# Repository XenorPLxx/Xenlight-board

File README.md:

# Xenlight-board
In action: https://www.youtube.com/watch?v=SORMGCwLncw

Windows app: https://github.com/XenorPLxx/Xenlight

Atmega16 code: https://github.com/XenorPLxx/Xenlight-driver

EAGLE Schematics: https://github.com/XenorPLxx/Xenlight-board

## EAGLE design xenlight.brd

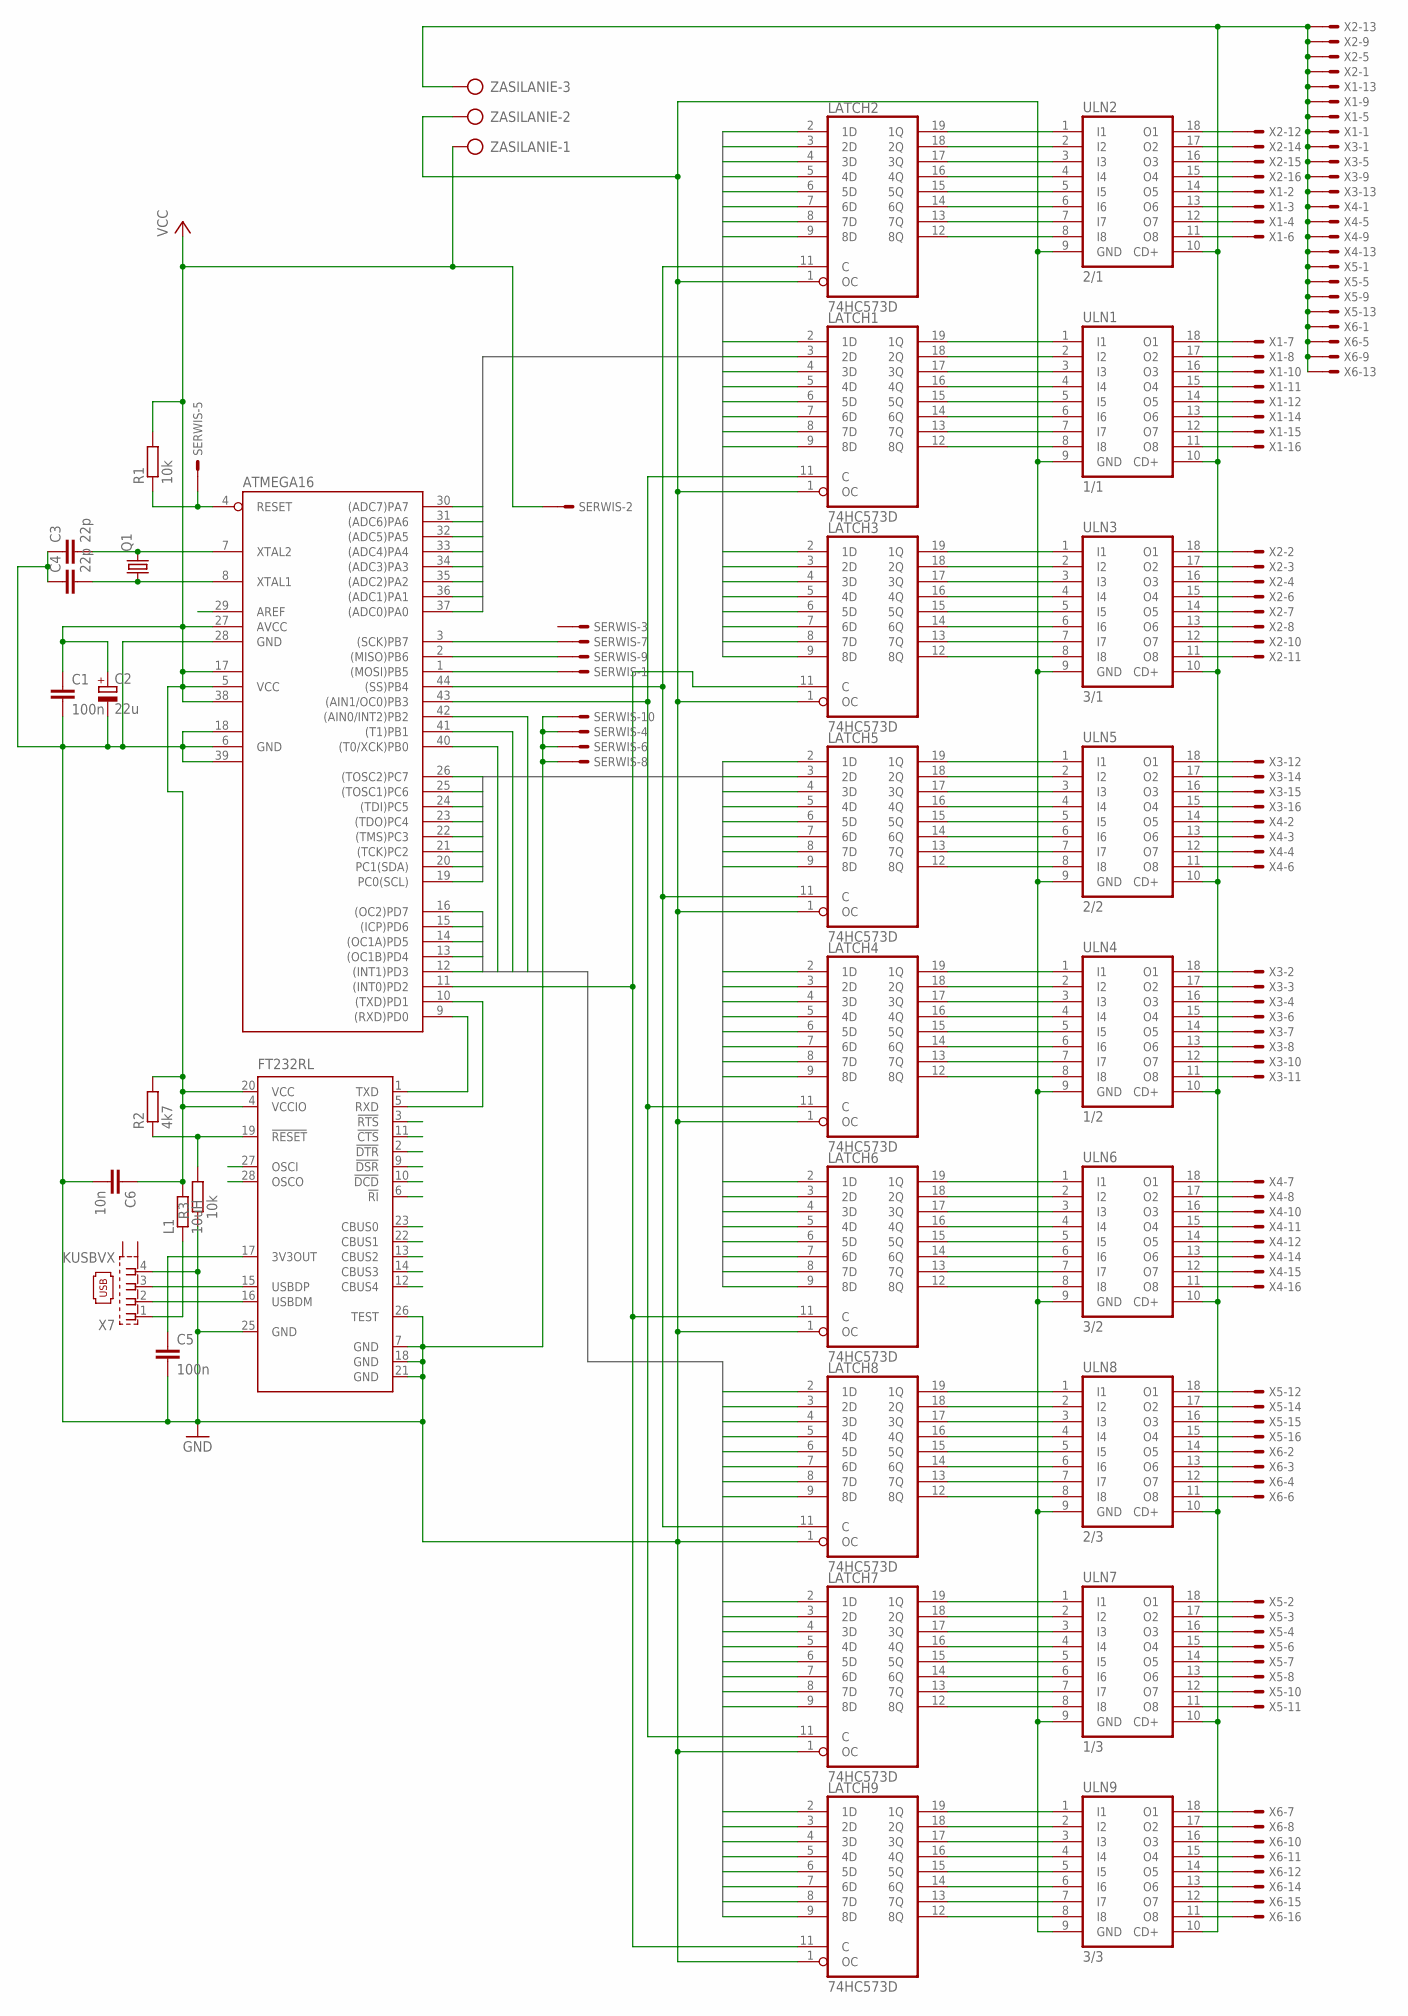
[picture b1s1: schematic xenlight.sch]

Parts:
ATMEGA16: MEGA16-A; TQFP44
C1, C5: 100n; C1206
C2: 22u; E1,8-4
C3, C4: 22p; C1206
C6: 10n; C1206
FT232RL: FT232RL; SSOP28
L1: 10uH; R1206
LATCH1, LATCH2, LATCH3, LATCH4, LATCH5, LATCH6, LATCH7, LATCH8, LATCH9: 74HC573D; SO20W
Q1: CRYSTALHC49UP; HC49UP
R1, R3: 10k; R0805
R2: 4k7; R0805
SERWIS: 057-010-1
ULN1: 1/1; SO18W
ULN2: 2/1; SO18W
ULN3: 3/1; SO18W
ULN4: 1/2; SO18W
ULN5: 2/2; SO18W
ULN6: 3/2; SO18W
ULN7: 1/3; SO18W
ULN8: 2/3; SO18W
ULN9: 3/3; SO18W
X1, X2, X3, X4, X5, X6: 057-016-1
X7: KUSBVX
ZASILANIE: AK300/3

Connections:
12V: ULN1.10 (CD+), ULN2.10 (CD+), ULN3.10 (CD+), ULN4.10 (CD+), ULN5.10 (CD+), ULN6.10 (CD+), ULN7.10 (CD+), ULN8.10 (CD+), ULN9.10 (CD+), X1.1, X1.5, X1.9, X1.13, X2.1, X2.5, X2.9, X2.13, X3.1, X3.5, X3.9, X3.13, X4.1, X4.5, X4.9, X4.13, X5.1, X5.5, X5.9, X5.13, X6.1, X6.5, X6.9, X6.13, ZASILANIE.3
GND: ATMEGA16.6 (GND), ATMEGA16.18 (GND1), ATMEGA16.28 (GND), ATMEGA16.39 (GND2), C1.2, C2.-, C3.1, C4.1, C5.2, C6.2, FT232RL.7 (GND), FT232RL.18 (GND), FT232RL.21 (GND), FT232RL.25 (GND), FT232RL.26 (TEST), LATCH1.1 (OC), LATCH1.10 (GND), LATCH2.1 (OC), LATCH2.10 (GND), LATCH3.1 (OC), LATCH3.10 (GND), LATCH4.1 (OC), LATCH4.10 (GND), LATCH5.1 (OC), LATCH5.10 (GND), LATCH6.1 (OC), LATCH6.10 (GND), LATCH7.1 (OC), LATCH7.10 (GND), LATCH8.1 (OC), LATCH8.10 (GND), LATCH9.1 (OC), LATCH9.10 (GND), R3.1, SERWIS.4, SERWIS.6, SERWIS.8, SERWIS.10, ULN1.9 (GND), ULN2.9 (GND), ULN3.9 (GND), ULN4.9 (GND), ULN5.9 (GND), ULN6.9 (GND), ULN7.9 (GND), ULN8.9 (GND), ULN9.9 (GND), X7.4, ZASILANIE.2
unnamed: ATMEGA16.30 ((ADC7)PA7), LATCH1.9 (8D), LATCH2.9 (8D), LATCH3.9 (8D)
unnamed: ATMEGA16.31 ((ADC6)PA6), LATCH1.8 (7D), LATCH2.8 (7D), LATCH3.8 (7D)
unnamed: ATMEGA16.32 ((ADC5)PA5), LATCH1.7 (6D), LATCH2.7 (6D), LATCH3.7 (6D)
unnamed: ATMEGA16.33 ((ADC4)PA4), LATCH1.6 (5D), LATCH2.6 (5D), LATCH3.6 (5D)
unnamed: ATMEGA16.34 ((ADC3)PA3), LATCH1.5 (4D), LATCH2.5 (4D), LATCH3.5 (4D)
unnamed: ATMEGA16.35 ((ADC2)PA2), LATCH1.4 (3D), LATCH2.4 (3D), LATCH3.4 (3D)
unnamed: ATMEGA16.36 ((ADC1)PA1), LATCH1.3 (2D), LATCH2.3 (2D), LATCH3.3 (2D)
unnamed: ATMEGA16.37 ((ADC0)PA0), LATCH1.2 (1D), LATCH2.2 (1D), LATCH3.2 (1D)
unnamed: ATMEGA16.26 ((TOSC2)PC7), LATCH4.2 (1D), LATCH5.2 (1D), LATCH6.2 (1D)
unnamed: ATMEGA16.25 ((TOSC1)PC6), LATCH4.3 (2D), LATCH5.3 (2D), LATCH6.3 (2D)
unnamed: ATMEGA16.24 ((TDI)PC5), LATCH4.4 (3D), LATCH5.4 (3D), LATCH6.4 (3D)
unnamed: ATMEGA16.23 ((TDO)PC4), LATCH4.5 (4D), LATCH5.5 (4D), LATCH6.5 (4D)
unnamed: ATMEGA16.22 ((TMS)PC3), LATCH4.6 (5D), LATCH5.6 (5D), LATCH6.6 (5D)
unnamed: ATMEGA16.21 ((TCK)PC2), LATCH4.7 (6D), LATCH5.7 (6D), LATCH6.7 (6D)
unnamed: ATMEGA16.20 (PC1(SDA)), LATCH4.8 (7D), LATCH5.8 (7D), LATCH6.8 (7D)
unnamed: ATMEGA16.19 (PC0(SCL)), LATCH4.9 (8D), LATCH5.9 (8D), LATCH6.9 (8D)
unnamed: ATMEGA16.16 ((OC2)PD7), LATCH7.2 (1D), LATCH8.2 (1D), LATCH9.2 (1D)
unnamed: ATMEGA16.15 ((ICP)PD6), LATCH7.3 (2D), LATCH8.3 (2D), LATCH9.3 (2D)
unnamed: ATMEGA16.14 ((OC1A)PD5), LATCH7.4 (3D), LATCH8.4 (3D), LATCH9.4 (3D)
unnamed: ATMEGA16.13 ((OC1B)PD4), LATCH7.5 (4D), LATCH8.5 (4D), LATCH9.5 (4D)
unnamed: ATMEGA16.12 ((INT1)PD3), LATCH7.6 (5D), LATCH8.6 (5D), LATCH9.6 (5D)
unnamed: ATMEGA16.44 ((SS)PB4), LATCH2.11 (C), LATCH5.11 (C), LATCH8.11 (C)
unnamed: ATMEGA16.43 ((AIN1/OC0)PB3), LATCH1.11 (C), LATCH4.11 (C), LATCH7.11 (C)
unnamed: LATCH2.19 (1Q), ULN2.1 (I1)
unnamed: LATCH2.18 (2Q), ULN2.2 (I2)
unnamed: LATCH2.17 (3Q), ULN2.3 (I3)
unnamed: LATCH2.16 (4Q), ULN2.4 (I4)
unnamed: LATCH2.15 (5Q), ULN2.5 (I5)
unnamed: LATCH2.14 (6Q), ULN2.6 (I6)
unnamed: LATCH2.13 (7Q), ULN2.7 (I7)
unnamed: LATCH2.12 (8Q), ULN2.8 (I8)
unnamed: LATCH1.19 (1Q), ULN1.1 (I1)
unnamed: LATCH1.18 (2Q), ULN1.2 (I2)
unnamed: LATCH1.17 (3Q), ULN1.3 (I3)
unnamed: LATCH1.16 (4Q), ULN1.4 (I4)
unnamed: LATCH1.15 (5Q), ULN1.5 (I5)
unnamed: LATCH1.14 (6Q), ULN1.6 (I6)
unnamed: LATCH1.13 (7Q), ULN1.7 (I7)
unnamed: LATCH1.12 (8Q), ULN1.8 (I8)
unnamed: LATCH5.19 (1Q), ULN5.1 (I1)
unnamed: LATCH5.18 (2Q), ULN5.2 (I2)
unnamed: LATCH5.17 (3Q), ULN5.3 (I3)
unnamed: LATCH5.16 (4Q), ULN5.4 (I4)
unnamed: LATCH5.15 (5Q), ULN5.5 (I5)
unnamed: LATCH5.14 (6Q), ULN5.6 (I6)
unnamed: LATCH5.13 (7Q), ULN5.7 (I7)
unnamed: LATCH3.19 (1Q), ULN3.1 (I1)
unnamed: LATCH4.19 (1Q), ULN4.1 (I1)
unnamed: LATCH4.18 (2Q), ULN4.2 (I2)
unnamed: LATCH4.17 (3Q), ULN4.3 (I3)
unnamed: LATCH4.16 (4Q), ULN4.4 (I4)
unnamed: LATCH4.15 (5Q), ULN4.5 (I5)
unnamed: LATCH4.14 (6Q), ULN4.6 (I6)
unnamed: LATCH4.13 (7Q), ULN4.7 (I7)
unnamed: LATCH4.12 (8Q), ULN4.8 (I8)
unnamed: LATCH8.19 (1Q), ULN8.1 (I1)
unnamed: LATCH8.18 (2Q), ULN8.2 (I2)
unnamed: LATCH8.17 (3Q), ULN8.3 (I3)
unnamed: LATCH8.16 (4Q), ULN8.4 (I4)
unnamed: LATCH8.15 (5Q), ULN8.5 (I5)
unnamed: LATCH3.18 (2Q), ULN3.2 (I2)
unnamed: ULN4.18 (O1), X3.2
unnamed: LATCH3.17 (3Q), ULN3.3 (I3)
unnamed: LATCH7.19 (1Q), ULN7.1 (I1)
unnamed: LATCH7.18 (2Q), ULN7.2 (I2)
unnamed: LATCH7.17 (3Q), ULN7.3 (I3)
unnamed: LATCH7.16 (4Q), ULN7.4 (I4)
unnamed: LATCH7.15 (5Q), ULN7.5 (I5)
unnamed: LATCH3.16 (4Q), ULN3.4 (I4)
unnamed: LATCH3.15 (5Q), ULN3.5 (I5)
unnamed: LATCH3.14 (6Q), ULN3.6 (I6)
unnamed: LATCH3.13 (7Q), ULN3.7 (I7)
unnamed: LATCH3.12 (8Q), ULN3.8 (I8)
unnamed: ATMEGA16.11 ((INT0)PD2), LATCH3.11 (C), LATCH6.11 (C), LATCH9.11 (C)
unnamed: LATCH6.19 (1Q), ULN6.1 (I1)
unnamed: LATCH6.18 (2Q), ULN6.2 (I2)
unnamed: LATCH6.17 (3Q), ULN6.3 (I3)
unnamed: LATCH6.16 (4Q), ULN6.4 (I4)
unnamed: LATCH6.15 (5Q), ULN6.5 (I5)
unnamed: LATCH6.14 (6Q), ULN6.6 (I6)
unnamed: LATCH6.13 (7Q), ULN6.7 (I7)
unnamed: LATCH6.12 (8Q), ULN6.8 (I8)
unnamed: LATCH9.19 (1Q), ULN9.1 (I1)
unnamed: LATCH9.18 (2Q), ULN9.2 (I2)
unnamed: LATCH9.17 (3Q), ULN9.3 (I3)
unnamed: LATCH9.16 (4Q), ULN9.4 (I4)
unnamed: LATCH9.15 (5Q), ULN9.5 (I5)
unnamed: LATCH9.14 (6Q), ULN9.6 (I6)
unnamed: LATCH9.13 (7Q), ULN9.7 (I7)
unnamed: LATCH9.12 (8Q), ULN9.8 (I8)
unnamed: ULN3.18 (O1), X2.2
unnamed: ULN3.17 (O2), X2.3
unnamed: ULN3.16 (O3), X2.4
unnamed: ULN3.15 (O4), X2.6
unnamed: ULN3.14 (O5), X2.7
unnamed: ULN3.13 (O6), X2.8
unnamed: ULN3.12 (O7), X2.10
unnamed: ULN3.11 (O8), X2.11
unnamed: ULN2.18 (O1), X2.12
unnamed: ULN2.17 (O2), X2.14
unnamed: ULN2.16 (O3), X2.15
unnamed: ULN2.15 (O4), X2.16
unnamed: ULN2.14 (O5), X1.2
unnamed: ATMEGA16.3 ((SCK)PB7), SERWIS.7
unnamed: ATMEGA16.2 ((MISO)PB6), SERWIS.9
unnamed: ATMEGA16.1 ((MOSI)PB5), SERWIS.1
unnamed: ULN2.13 (O6), X1.3
unnamed: ULN2.12 (O7), X1.4
unnamed: LATCH5.12 (8Q), ULN5.8 (I8)
unnamed: ULN2.11 (O8), X1.6
unnamed: ULN1.18 (O1), X1.7
unnamed: ULN1.17 (O2), X1.8
unnamed: ULN1.16 (O3), X1.10
unnamed: ULN1.15 (O4), X1.11
unnamed: ATMEGA16.8 (XTAL1), C4.2, Q1.1
unnamed: ATMEGA16.7 (XTAL2), C3.2, Q1.2
unnamed: FT232RL.15 (USBDP), X7.3
unnamed: ATMEGA16.9 ((RXD)PD0), FT232RL.1 (TXD)
unnamed: ATMEGA16.10 ((TXD)PD1), FT232RL.5 (RXD)
unnamed: FT232RL.16 (USBDM), X7.2
unnamed: L1.1, X7.1
unnamed: LATCH8.14 (6Q), ULN8.6 (I6)
unnamed: FT232RL.19 (!RESET), R2.1, R3.2
unnamed: C5.1, FT232RL.17 (3V3OUT)
unnamed: ATMEGA16.4 (RESET), R1.1, SERWIS.5
unnamed: LATCH8.13 (7Q), ULN8.7 (I7)
unnamed: LATCH8.12 (8Q), ULN8.8 (I8)
unnamed: LATCH7.14 (6Q), ULN7.6 (I6)
unnamed: LATCH7.13 (7Q), ULN7.7 (I7)
unnamed: LATCH7.12 (8Q), ULN7.8 (I8)
unnamed: ULN1.14 (O5), X1.12
unnamed: ULN1.13 (O6), X1.14
unnamed: ULN1.12 (O7), X1.15
unnamed: ULN1.11 (O8), X1.16
unnamed: ULN4.17 (O2), X3.3
unnamed: ATMEGA16.42 ((AIN0/INT2)PB2), LATCH7.7 (6D), LATCH8.7 (6D), LATCH9.7 (6D)
unnamed: ATMEGA16.41 ((T1)PB1), LATCH7.8 (7D), LATCH8.8 (7D), LATCH9.8 (7D)
unnamed: ATMEGA16.40 ((T0/XCK)PB0), LATCH7.9 (8D), LATCH8.9 (8D), LATCH9.9 (8D)
unnamed: ULN4.16 (O3), X3.4
unnamed: ULN4.15 (O4), X3.6
unnamed: ULN4.14 (O5), X3.7
unnamed: ULN4.13 (O6), X3.8
unnamed: ULN4.12 (O7), X3.10
unnamed: ULN4.11 (O8), X3.11
unnamed: ULN5.18 (O1), X3.12
unnamed: ULN5.17 (O2), X3.14
unnamed: ULN5.16 (O3), X3.15
unnamed: ULN5.15 (O4), X3.16
unnamed: ULN5.14 (O5), X4.2
unnamed: ULN5.13 (O6), X4.3
unnamed: ULN5.12 (O7), X4.4
unnamed: ULN5.11 (O8), X4.6
unnamed: ULN6.18 (O1), X4.7
unnamed: ULN6.17 (O2), X4.8
unnamed: ULN6.16 (O3), X4.10
unnamed: ULN6.15 (O4), X4.11
unnamed: ULN6.14 (O5), X4.12
unnamed: ULN6.13 (O6), X4.14
unnamed: ULN6.12 (O7), X4.15
unnamed: ULN6.11 (O8), X4.16
unnamed: ULN7.18 (O1), X5.2
unnamed: ULN7.17 (O2), X5.3
unnamed: ULN7.16 (O3), X5.4
unnamed: ULN7.15 (O4), X5.6
unnamed: ULN7.14 (O5), X5.7
unnamed: ULN7.13 (O6), X5.8
unnamed: ULN7.12 (O7), X5.10
unnamed: ULN7.11 (O8), X5.11
unnamed: ULN8.18 (O1), X5.12
unnamed: ULN8.17 (O2), X5.14
unnamed: ULN8.16 (O3), X5.15
unnamed: ULN8.15 (O4), X5.16
unnamed: ULN8.14 (O5), X6.2
unnamed: ULN8.13 (O6), X6.3
unnamed: ULN8.12 (O7), X6.4
unnamed: ULN8.11 (O8), X6.6
unnamed: ULN9.18 (O1), X6.7
unnamed: ULN9.17 (O2), X6.8
unnamed: ULN9.16 (O3), X6.10
unnamed: ULN9.15 (O4), X6.11
unnamed: ULN9.14 (O5), X6.12
unnamed: ULN9.13 (O6), X6.14
unnamed: ULN9.12 (O7), X6.15
unnamed: ULN9.11 (O8), X6.16
VCC: ATMEGA16.5 (VCC), ATMEGA16.17 (VCC1), ATMEGA16.27 (AVCC), ATMEGA16.38 (VCC2), C1.1, C2.+, C6.1, FT232RL.4 (VCCIO), FT232RL.20 (VCC), L1.2, LATCH1.20 (VCC), LATCH2.20 (VCC), LATCH3.20 (VCC), LATCH4.20 (VCC), LATCH5.20 (VCC), LATCH6.20 (VCC), LATCH7.20 (VCC), LATCH8.20 (VCC), LATCH9.20 (VCC), R1.2, R2.2, SERWIS.2, ZASILANIE.1

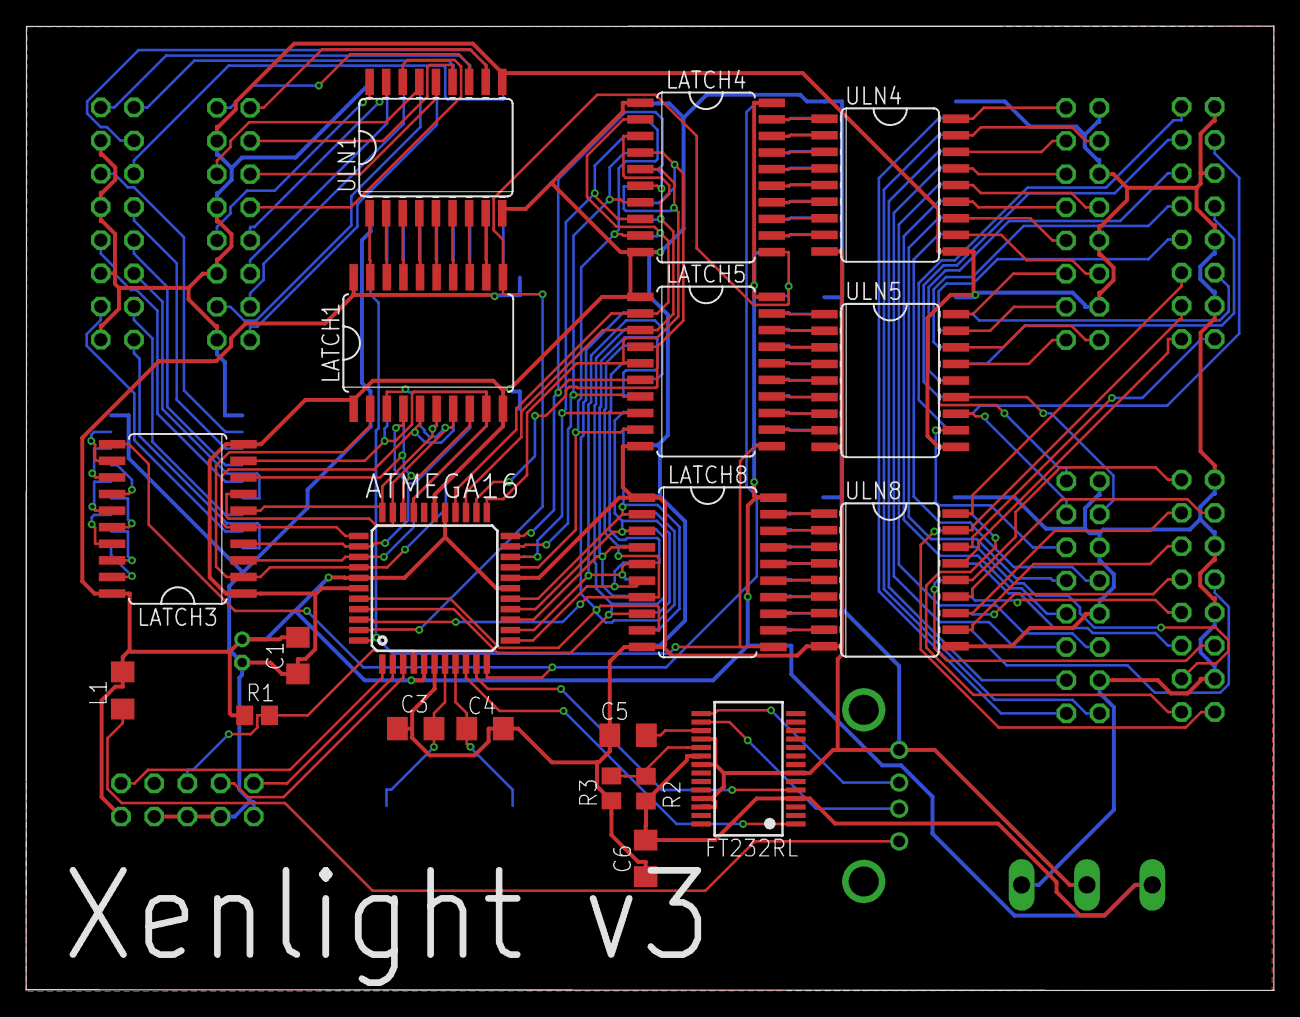
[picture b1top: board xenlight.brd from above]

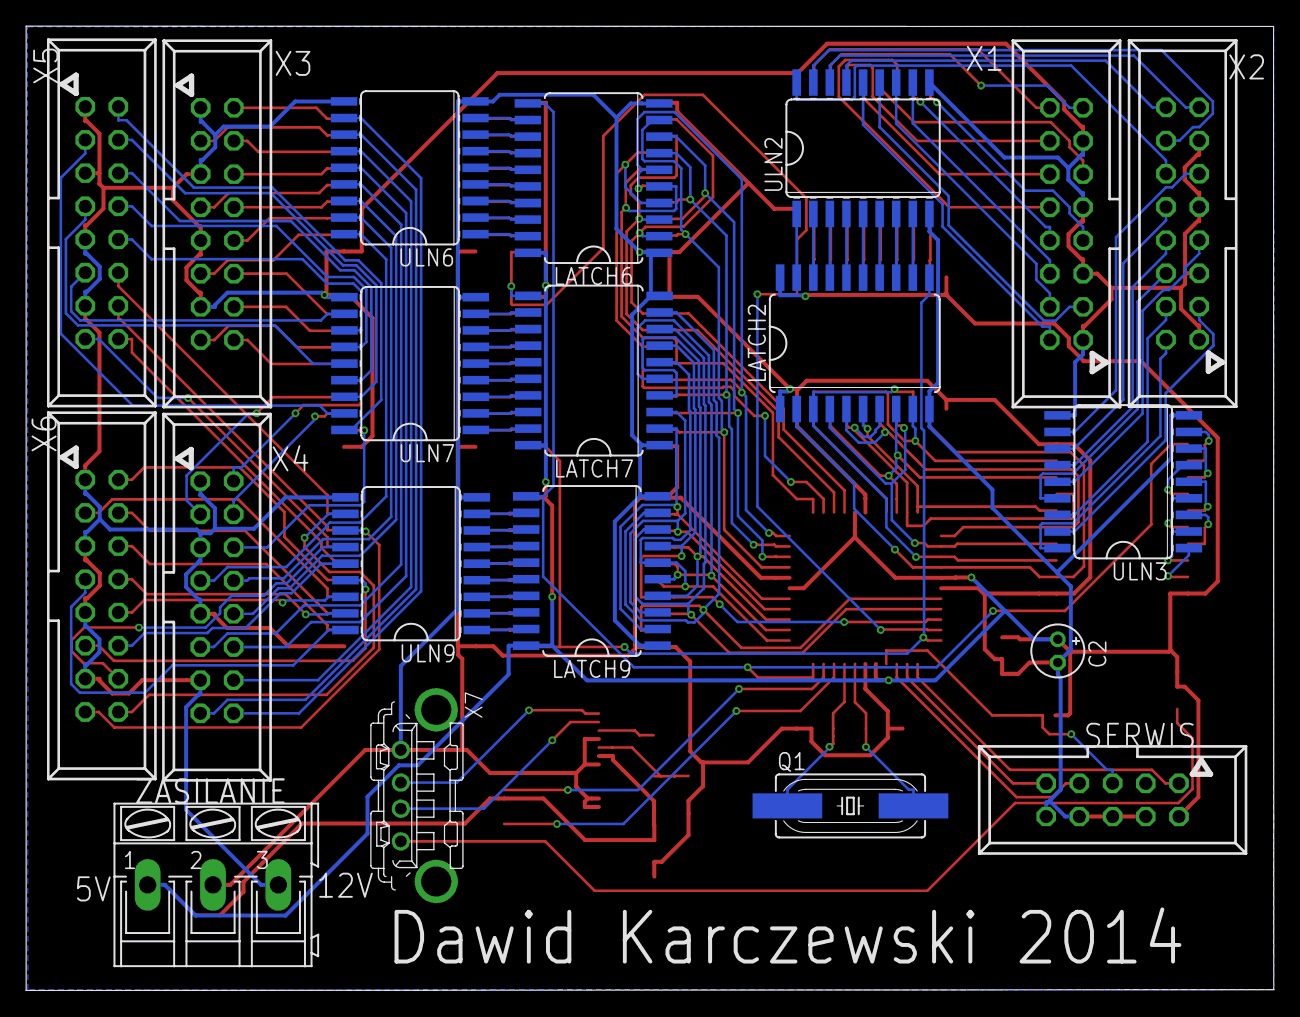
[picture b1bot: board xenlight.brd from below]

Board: 2 copper layers, 95.5 x 73.8 mm, 40 parts (20 on the bottom side), 187 nets.

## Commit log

2017-06-21 First version of board, designed for homemade production.
2017-06-21 Second version of board, not for homemade production.
2017-06-21 Attempt to reduce size.
2017-06-21 Another attempts to reduce size and reroute.
